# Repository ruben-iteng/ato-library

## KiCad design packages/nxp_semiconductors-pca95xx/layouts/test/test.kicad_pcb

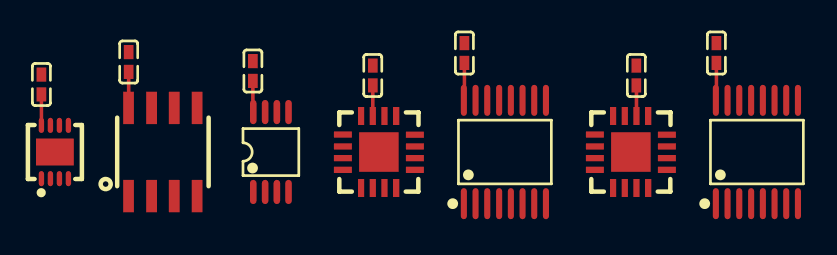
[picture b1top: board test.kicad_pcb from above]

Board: 2 copper layers, 14 parts (0 on the bottom side), 4 nets.

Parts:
C1, C2, C3, C4, C5, C6, C7: 100nF ±10% 16V X7R; C0402
U1: HVSON-8_L3.0-W3.0-P0.50-BL-EP
U2: SO-8_L4.9-W3.9-P1.27-LS6.0-BL
U3: TSSOP-8_L3.0-W3.0-P0.65-LS4.9-BL
U4, U6: HVQFN-16_L4.0-W4.0-P0.65-TL-EP2.2
U5, U7: TSSOP-16_L5.0-W4.4-P0.65-LS6.4-BL

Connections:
gnd: C1.2, C2.2, C3.2, C4.2, C5.2, C6.2, C7.2, U1.4, U1.9, U2.4, U3.4, U4.1, U4.6, U4.16, U4.17, U5.1, U5.2, U5.3, U5.8, U6.1, U6.6, U6.16, U6.17, U7.1, U7.2, U7.3, U7.8
scl: U1.6, U2.6, U3.6, U4.12, U5.14, U6.12, U7.14
sda: U1.7, U2.7, U3.7, U4.13, U5.15, U6.13, U7.15
vdd: C1.1, C2.1, C3.1, C4.1, C5.1, C6.1, C7.1, U1.8, U2.8, U3.8, U4.14, U4.15, U5.16, U6.14, U6.15, U7.16

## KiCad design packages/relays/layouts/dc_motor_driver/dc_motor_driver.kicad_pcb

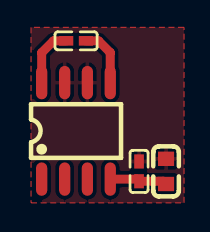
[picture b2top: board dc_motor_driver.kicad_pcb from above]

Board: 2 copper layers, 4 parts (0 on the bottom side), 4 nets.

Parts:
C1: 100nF ±10% 16V X7R; C0402
C2: 4.7µF ±10% 16V X5R; C0603
C3: 100pF ±5% 50V C0G; C0402
U1: SOP-8_L4.9-W3.9-P1.27-LS6.0-BL

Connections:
OUTA: C3.1, U1.8
VDD: C1.1, C2.1, U1.4
gnd: C1.2, C2.2, U1.6, U1.7
gnd-1: C3.2, U1.5
